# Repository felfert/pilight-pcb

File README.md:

# pilight-pcb

A minimalistic pcb for connecting a receiver and transmitter for pilight to a raspberry.

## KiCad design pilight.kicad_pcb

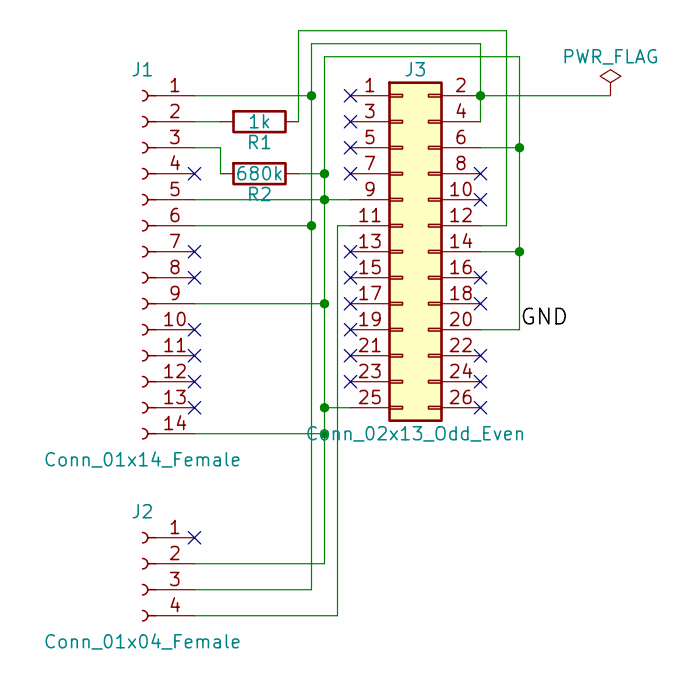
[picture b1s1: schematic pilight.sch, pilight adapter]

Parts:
J1: Conn_01x14_Female; Socket_Strip_Angled_1x14_Pitch2.54mm
J2: Conn_01x04_Female; Socket_Strip_Angled_1x04_Pitch2.54mm
J3: Conn_02x13_Odd_Even; Pin_Header_Straight_2x13_Pitch2.54mm
R1: 1k; R_Axial_DIN0207_L6.3mm_D2.5mm_P7.62mm_Horizontal
R2: 680k; R_Axial_DIN0207_L6.3mm_D2.5mm_P7.62mm_Horizontal

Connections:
/GND: J1.5, J1.9, J1.14, J2.2, J3.6, J3.9, J3.14, J3.20, J3.25, R2.1
unnamed: J1.1, J1.6, J2.3, J3.2, J3.4
unnamed: J1.2, R1.2
unnamed: J1.3, R2.2
unnamed: J2.4, J3.11
unnamed: J3.12, R1.1

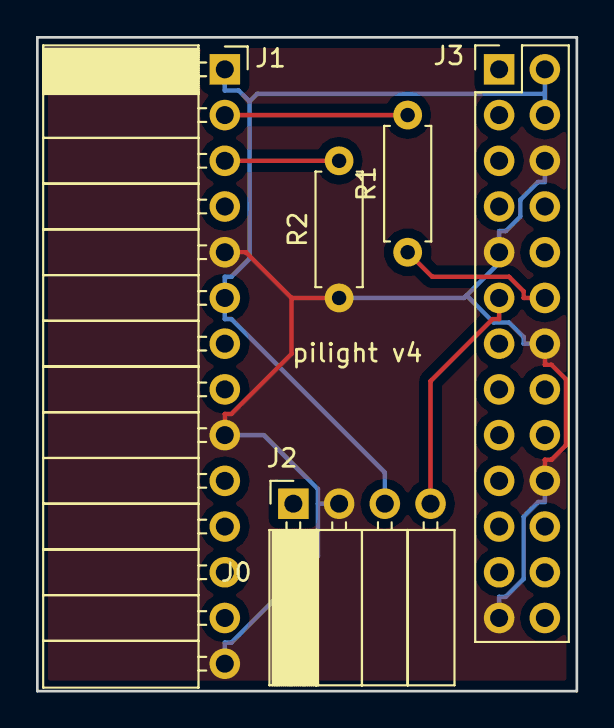
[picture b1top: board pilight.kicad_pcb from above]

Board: 2 copper layers, 30.0 x 36.3 mm, 6 parts (0 on the bottom side), 6 nets.

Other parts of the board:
J0: RX-Ant; SolderWirePad_single_0-8mmDrill

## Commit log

2018-11-10 Initial add
2018-11-10 Add lib cache
2018-11-10 Updated initial doc
